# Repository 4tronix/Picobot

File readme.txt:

Picobot Released Files
======================

All files are Licensed under Creative Commons BY-SA
See creativecommons.org/licenses/by-sa/3.0/ for details

CP2102 programming cable requires drivers from: silabs.com/products/mcu/Pages/USBtoUARTBridgeVCPDrivers.aspx

When using the Arduino IDE, select board type UNO. The Picobot is fully compatible with the UNO

Note - v1.3 and later Versions
==============================
Version 1.3 and 1.4 of the Picobot PCB use neopixel LEDs instead of standard RGB LEDs and this means that they
are individually addressable so you can have different colours on the left and the right.

The versions of the software below with the suffix '2' indicate that they are built for use with neopixels

You must install the Arduino library FastLED2 for these examples to work.

Picobot Software
================
DemoAll - Uses the Mode button to switch between 5 different demos. After pressing the button it flashes the LEDs the number of times for the following demos:
	1. Flash all the LEDs
	2. Line Follower
	3. Light Seeker
	4. Obstacle avoider
	5. Constant distance
AllLeds - Lights all the LEDs
BlinkTest - Flashes all the LEDs one at a time
AnalogTest - outputs analog values from light and line following sensors to Serial Monitor
MotorTest - Turns the motors Forwards, Reverse, Spin Left, Spin Right, Halt in turn
Utra - Outputs the distance reading from teh Ultrasonic sensor to the Serial Monitor
Runaway - Uses the Picobot library and ultrasonic sensor to avoid objects
LineFollower - Simple line follower script using the RGB LEDs to show direction

Picobot Schematics
==================
Picobot<xy>.sch is the Eagle schematic for version x.y
Picobot<xy>.brd is the Eagle board file for version x.y

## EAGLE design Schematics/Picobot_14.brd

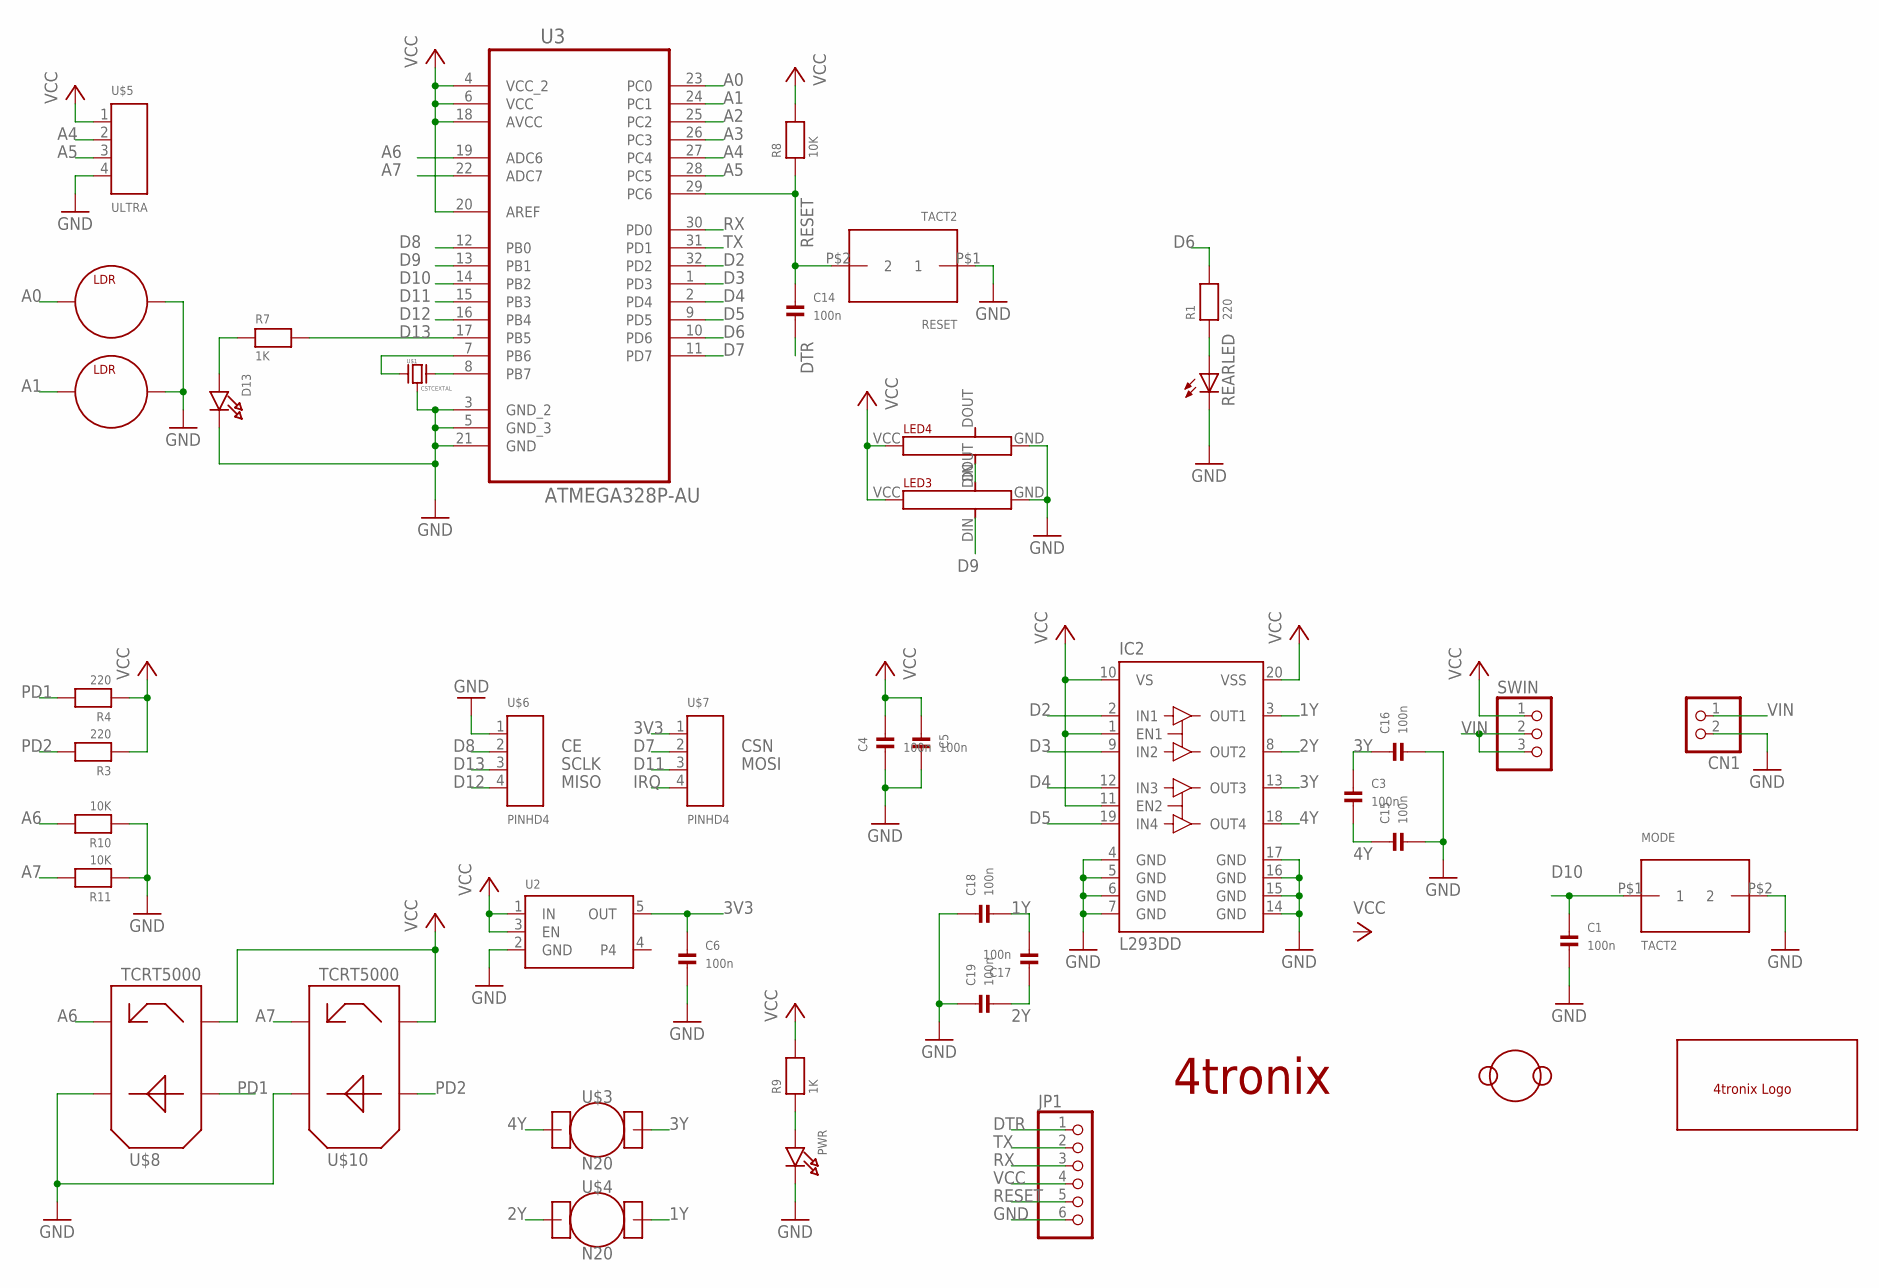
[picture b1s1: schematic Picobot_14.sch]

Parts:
C1, C3, C4, C5, C6, C14, C15, C16, C17, C18, C19: 100n; _0603MP
CN1: JST_2PIN-THM; JST-PH-2-THM
D13: LED0805_NOOUTLINE; CHIPLED_0805_NOOUTLINE
IC2: L293DD; SO20
JP1: PINHD-1X6CB; 1X06-CLEANBIG
LDR1, LDR2: LDR
LED3, LED4: WS2812B
MODE: TACT2; TACT2-PIN
PWR: LED0805_NOOUTLINE; CHIPLED_0805_NOOUTLINE
R1, R3, R4: 220; 0603-MINI
R7, R9: 1K; 0603-MINI
R8, R10, R11: 10K; 0603-MINI
REARLED: LED3MM
RESET: TACT2; TACT2-PIN
SWIN: PINHD-1X3CB; 1X03-CLEANBIG
U2: VREG_SOT23-5; SOT23-5
U3: ATMEGA328P-AU; QFP80P900X900X120-32N
U$1: CSTCEXTAL
U$2: LOGO
U$3, U$4: N20
U$5: ULTRA; PINHD4
U$6, U$7: PINHD4
U$8, U$10: TCRT5000
U$9: DFRBALL

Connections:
1Y: C17.2, C18.2, IC2.3 (OUT1), U$4.MTRA (MTRB)
2Y: C17.1, C19.2, IC2.8 (OUT2), U$4.MTRB (MTRA)
3V3: C6.1, U2.5 (OUT), U$7.1
3Y: C3.1, C16.1, IC2.13 (OUT3), U$3.MTRA (MTRB)
4Y: C3.2, C15.1, IC2.18 (OUT4), U$3.MTRB (MTRA)
A0: LDR1.A, U3.23 (PC0)
A1: LDR2.A, U3.24 (PC1)
A2: U3.25 (PC2)
A3: U3.26 (PC3)
A4: U3.27 (PC4), U$5.2
A5: U3.28 (PC5), U$5.3
A6: R10.2, U3.19 (ADC6), U$8.TR2
A7: R11.2, U3.22 (ADC7), U$10.TR2
D2: IC2.2 (IN1), U3.32 (PD2)
D3: IC2.9 (IN2), U3.1 (PD3)
D4: IC2.12 (IN3), U3.2 (PD4)
D5: IC2.19 (IN4), U3.9 (PD5)
D6: R1.2, U3.10 (PD6)
D7: U3.11 (PD7), U$7.2
D8: U3.12 (PB0), U$6.2
D9: LED3.DIN (DI), U3.13 (PB1)
D10: C1.1, MODE.P$1 (1), U3.14 (PB2)
D11: U3.15 (PB3), U$7.3
D12: U3.16 (PB4), U$6.4
D13: R7.2, U3.17 (PB5), U$6.3
DTR: C14.2, JP1.1
GND: C1.2, C4.2, C5.2, C6.2, C15.2, C16.2, C18.1, C19.1, CN1.2 (1), D13.C, IC2.4 (GND), IC2.5 (GND), IC2.6 (GND), IC2.7 (GND), IC2.14 (GND), IC2.15 (GND), IC2.16 (GND), IC2.17 (GND), JP1.6, LDR1.K, LDR2.K, LED3.GND, LED4.GND, MODE.P$2 (2), PWR.C, R10.1, R11.1, REARLED.K (C), RESET.P$1 (1), U2.2 (GND), U3.3 (GND_2), U3.5 (GND_3), U3.21 (GND), U$1.G, U$5.4, U$6.1, U$8.LED2, U$10.LED2
IRQ: U$7.4
unnamed: D13.A, R7.1
unnamed: R1.1, REARLED.A
unnamed: U3.7 (PB6), U$1.X1
unnamed: U3.8 (PB7), U$1.X2
unnamed: LED3.DOUT (DO), LED4.DIN (DI)
unnamed: PWR.A, R9.1
PD1: R4.2, U$8.LED1
PD2: R3.2, U$10.LED1
RESET: C14.1, JP1.5, R8.1, RESET.P$2 (2), U3.29 (PC6)
RX: JP1.3, U3.30 (PD0)
TX: JP1.2, U3.31 (PD1)
VCC: C4.1, C5.1, IC2.1 (EN1), IC2.10 (VS), IC2.11 (EN2), IC2.20 (VSS), JP1.4, LED3.VCC, LED4.VCC, R3.1, R4.1, R8.2, R9.2, SWIN.1, U2.1 (IN), U2.3 (EN), U3.4 (VCC_2), U3.6 (VCC), U3.18 (AVCC), U3.20 (AREF), U$5.1, U$8.TR1, U$10.TR1
VIN: CN1.1 (2), SWIN.2, SWIN.3

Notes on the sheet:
4tronix
SCLK
MISO
CSN
MOSI

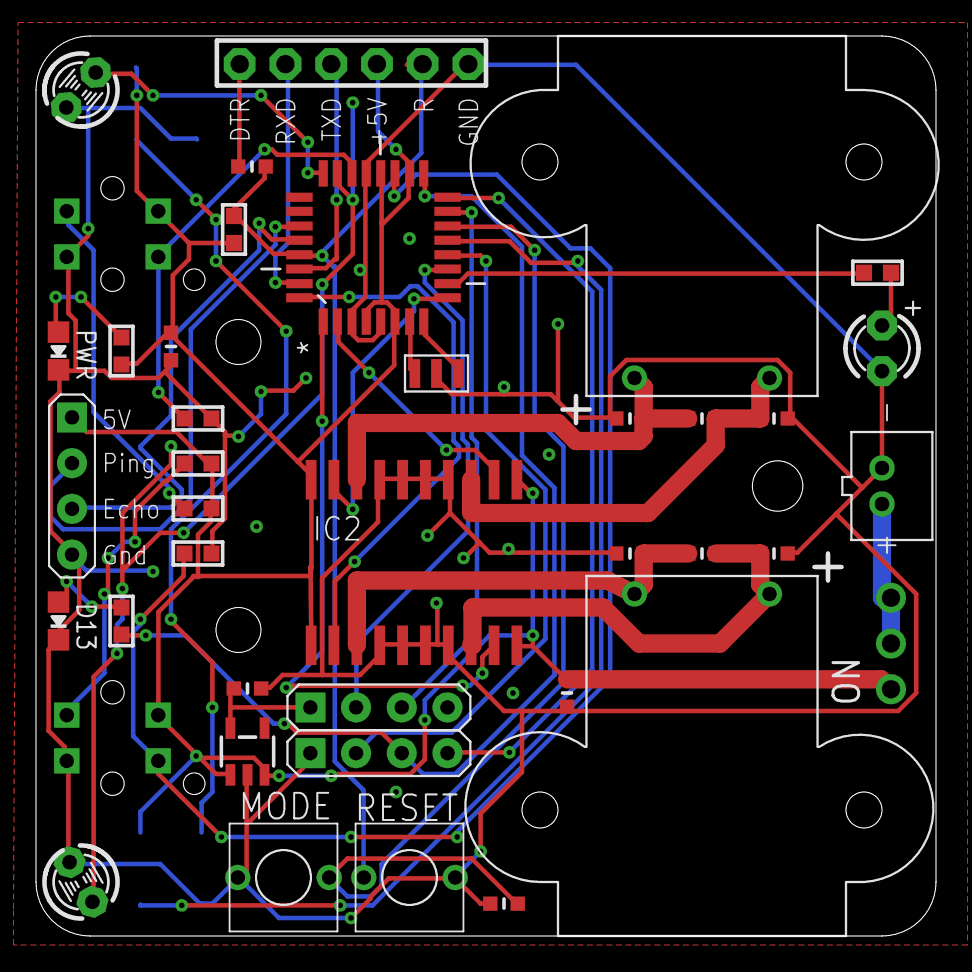
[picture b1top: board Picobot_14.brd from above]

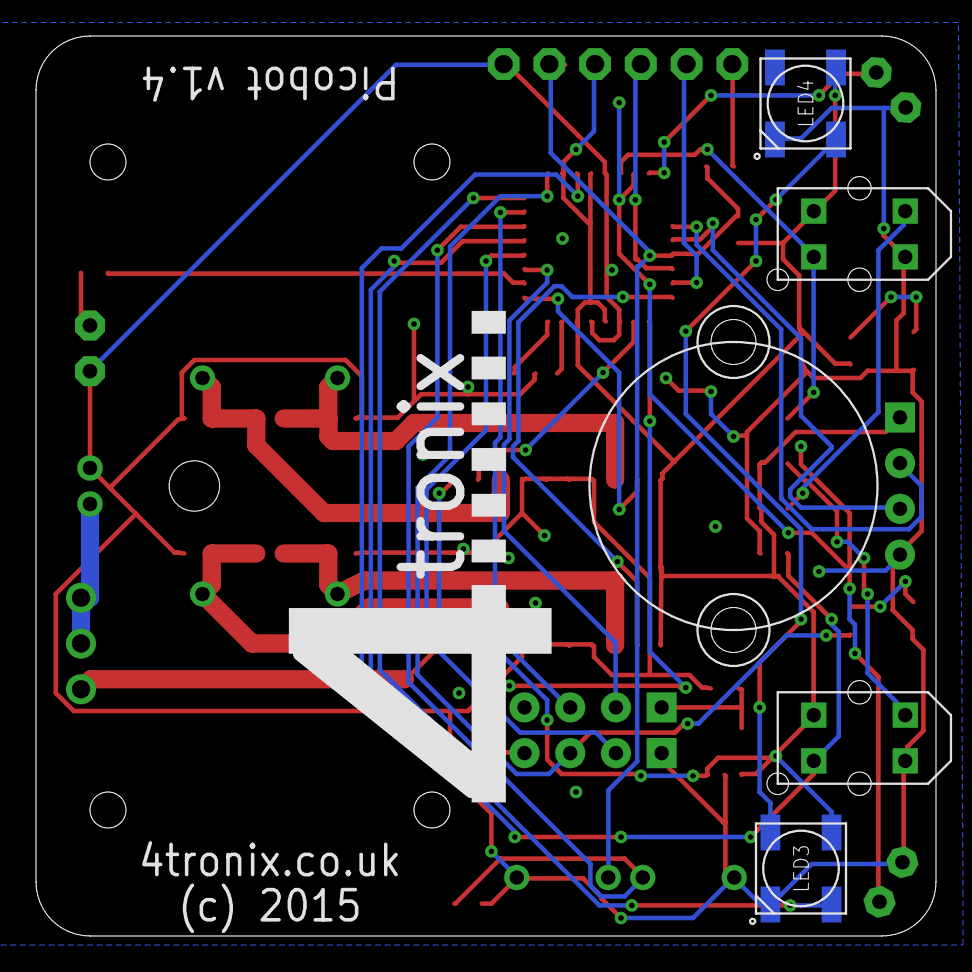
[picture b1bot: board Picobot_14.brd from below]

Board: 2 copper layers, 50.0 x 50.0 mm, 44 parts (6 on the bottom side), 38 nets.

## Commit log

2015-01-10 :lollipop: Added .gitattributes & .gitignore files
2015-01-10 First Release of Software
2015-01-10 Added Pinout Info
2015-01-10 Added reset pin info
2015-01-12 Revised Motor Pins for V1.0
2015-01-12 Added Line Follower
    New Line Follower script and updates to the licence information
2015-01-12 Updated Readme to show LineFollower
2015-02-16 New Demo App
    Added multifunction demo sketch as the installed sketch when shipping
2015-02-16 Corrected Comments
2015-08-03 Update for v1.3 and Later
    Added support for neopixels
2015-08-03 Added FastLED2 Library
    Arduino Library file required for Neopixel examples
2015-08-03 Schematic Updates
    Includes neopixels and layout changes

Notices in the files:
Schematics/Picobot_14.brd:
(c) 2015
parts and their libraries:
microbuilder: This work is placed in the public domain, and may be freely used for commercial and non-commercial work with the following conditions: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
